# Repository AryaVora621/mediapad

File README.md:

# Mediapad

a custom USB media controller I designed from scratch. three mechanical switches for playback, a rotary encoder for volume, and a little OLED screen I'm still adding. built as part of [Hack Club's Hackpad program](https://stardance.hackclub.com/missions/hackpad/guide).

> **status:** PCB design done, case WIP in Onshape, OLED coming next

---

## what it does

plug it in over USB-C and it shows up as a keyboard. no drivers, no software. just works.

| control | action |
|---|---|
| key 1 | play / pause |
| key 2 | previous track |
| key 3 | next track |
| encoder (rotate) | volume up / down |
| encoder (click) | mute |

---

## what's in it

| part | details |
|---|---|
| Seeed Studio XIAO RP2040 | microcontroller, USB-C, runs CircuitPython |
| EC11 rotary encoder | 20 detents, built-in click |
| 3x MX-compatible switches | any MX switch works |
| SSD1306 OLED | 128x32, I2C — footprint on board, wiring it up next |
| custom PCB | 2-layer, designed in KiCad, ordered from JLCPCB |
| 3D printed case | designed in Onshape, v2 redesign in progress |

---

## firmware

running [KMK](https://github.com/KMKfw/kmk_firmware), which is keyboard firmware written in CircuitPython. the XIAO mounts as a USB drive when you plug it in, so changing keybindings is just editing `code.py` and saving. no reflashing needed.

```python
from kmk.kmk_keyboard import KMKKeyboard
from kmk.keys import KC
from kmk.modules.encoder import EncoderHandler

keyboard = KMKKeyboard()
encoder_handler = EncoderHandler()

keyboard.keymap = [[
    KC.MPLY,  # play / pause
    KC.MPRV,  # previous track
    KC.MNXT,  # next track
]]

encoder_handler.map = [[(KC.VOLU, KC.VOLD, KC.MUTE)]]
```

---

## pcb

designed in KiCad 8. two-layer board, all traces routed by hand. schematic and layout files are in the `Mediapad/` folder.

to open it: install KiCad 8, then open `Mediapad/Mediapad.kicad_pro`.

---

## current progress

- [x] PCB schematic + layout (KiCad)
- [ ] case redesign (Onshape v2, the v1 is literally just a box)
- [ ] add OLED to PCB revision
- [ ] solder and test the full build
- [ ] get the OLED showing track info

---

## project page

[mediapad.vercel.app](https://mediapad.vercel.app)

---

built by [arya vora](https://github.com/AryaVora621) as part of [Hack Club Hackpad](https://stardance.hackclub.com/missions/hackpad/guide)

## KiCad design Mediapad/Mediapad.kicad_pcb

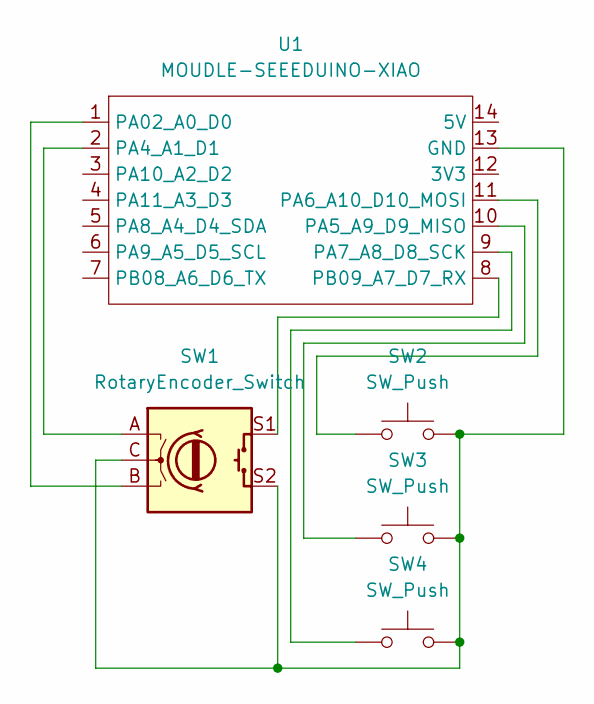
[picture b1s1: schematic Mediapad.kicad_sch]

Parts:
SW1: RotaryEncoder_Switch; RotaryEncoder_Alps_EC11E-Switch_Vertical_H20mm
SW2, SW3, SW4: SW_Push; MX-Solderable-1U
U1: MOUDLE-SEEEDUINO-XIAO; XIAO-Generic-Hybrid-14P-2.54-21X17.8MM

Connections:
unnamed: SW1.C, SW1.S2, SW2.2, SW3.2, SW4.2, U1.13 (GND)
unnamed: SW1.B, U1.1 (PA02_A0_D0)
unnamed: SW1.A, U1.2 (PA4_A1_D1)
unnamed: SW3.1, U1.10 (PA5_A9_D9_MISO)
unnamed: SW2.1, U1.11 (PA6_A10_D10_MOSI)
unnamed: SW4.1, U1.9 (PA7_A8_D8_SCK)
unnamed: SW1.S1, U1.8 (PB09_A7_D7_RX)

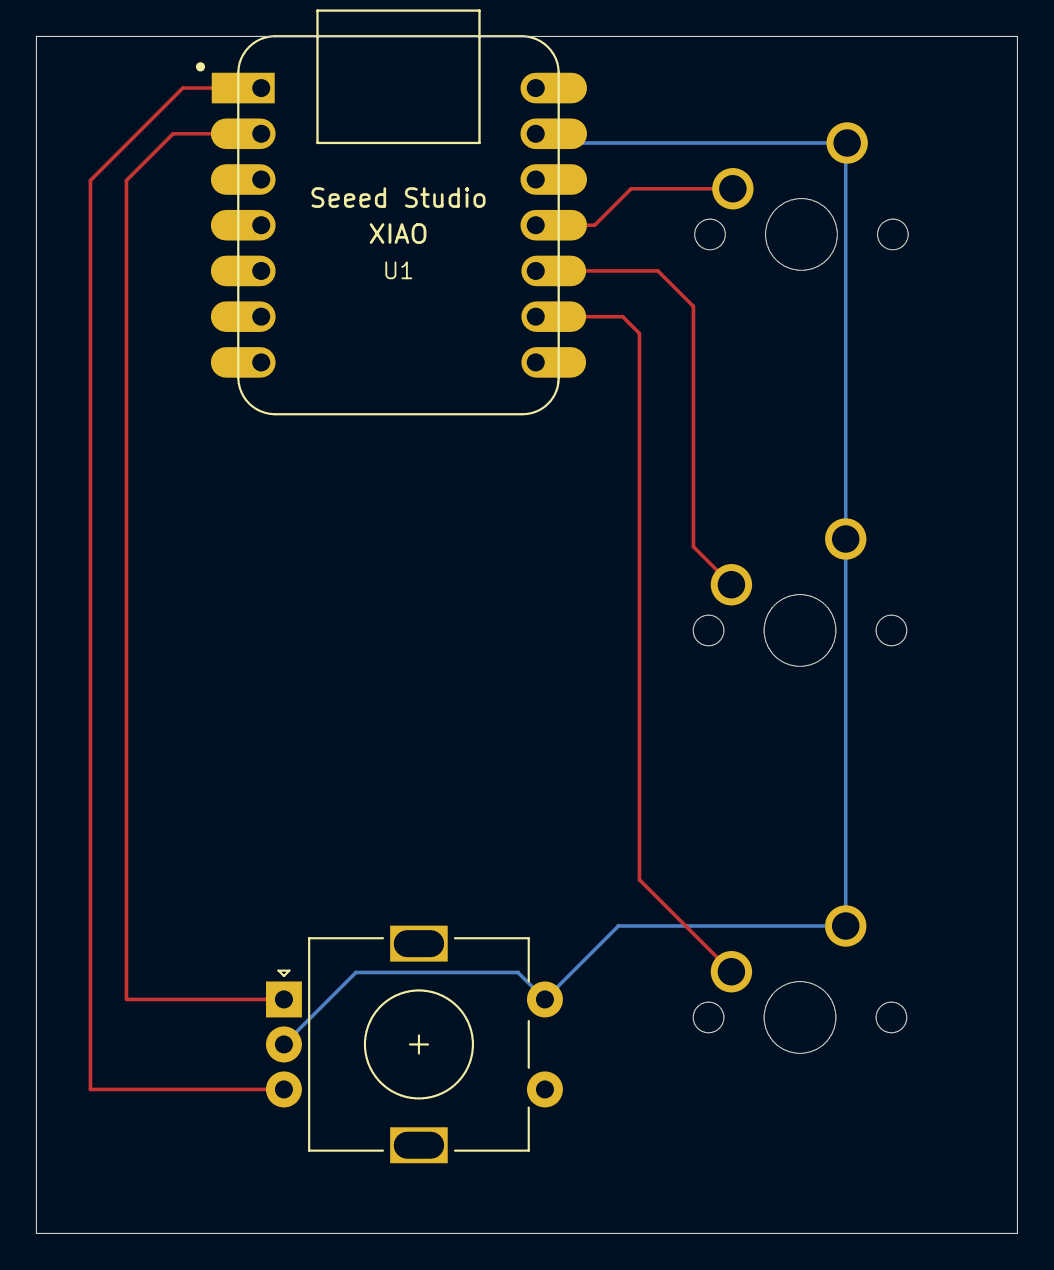
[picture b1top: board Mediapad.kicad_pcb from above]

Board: 2 copper layers, 54.5 x 66.5 mm, 5 parts (0 on the bottom side), 7 nets.
